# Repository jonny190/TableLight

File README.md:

# TableLight

A 3D-printable, battery-powered, USB-C rechargeable table lamp in the classic "Poldina" shape - honeycomb
disc base, thin stem, down-firing cone shade with a white top - running [WLED](https://kno.wled.ge/) on an
ESP32, with a capacitive touch pad hidden under the white top plate.

| | |
|---|---|
| Size | Ø118 x 36 mm base, Ø22 stem, shade Ø140 -> Ø104 x 120 mm, 279 mm tall overall |
| Light | 24-LED SK6812 RGBW (or WS2812B) ring under the head, shining down through a diffuser; optional second 16-LED ring |
| Power | 1 **or** 2 x 18650 Li-ion in parallel (1S) in the base, USB-C charging (1 A) in the base, runs while charging |
| Control | WLED app / web UI / Home Assistant + touch on the white top (ESP32 native touch) |
| Electronics | one custom Ø110 mm PCB in the base (KiCad board + PCBWay Gerber/BOM/CPL package included); flashes WLED over the same USB-C port |
| Runtime | ~5 h at full reading brightness, ~12 h at mood brightness with two 3500 mAh cells (half with one cell) |

## What is in this repository

```
cad/tablelight.py          parametric CAD (Python: trimesh + manifold) - ALL dimensions live here
cad/stl/                   ready-to-print STL files (6 parts)
hardware/pcb/              custom controller PCB: SKiDL circuit, KiCad 7 board (kicad/), PCBWay fab package
                           (fab/: Gerbers, drill, BOM, pick-and-place), board generator, design notes
firmware/wled/             WLED build override + settings for this lamp
docs/BOM.md                complete bill of materials (printed parts, electronics, hardware, consumables)
docs/PRINTING.md           print settings and orientation per part
docs/ASSEMBLY.md           step-by-step build
docs/WLED_SETUP.md         WLED configuration (pins, 2D matrix, touch button, battery, current limit)
docs/images/               renders, section drawing, PCB placement, block diagram
```

## The parts

| STL | Qty | What it does |
|---|---|---|
| `base_shell.stl` | 1 | Honeycomb-topped base disc: the PCB hangs under its deck (components facing down), USB-C, power switch and charge LEDs in the side wall, 1-2 x 18650 inside |
| `base_bottom_plate.stl` | 1 | Screw-on floor with rubber feet; remove it to reach the batteries, buttons and connectors |
| `stem.stl` | 1 | Ø22 hollow stem with a Ø40 foot flange; screwed to the deck from below, carries the wires to the head |
| `head_plate.stl` | 1 | White top: stem socket, two LED-ring channels on the underside, skirt that the shade screws to, touch-pad recess |
| `cone_shade.stl` | 1 | Opaque cone Ø140 -> Ø104, open at the bottom; 3 nubs hold the diffuser, 3 radial screws hold it to the head |
| `head_diffuser.stl` | 1 | Ø104 translucent disc 14 mm under the LED ring so you never see bare LEDs from below |

Section through the assembled lamp (all clearances are modelled, nothing is glued):

## Electronics in one picture

Power path: USB-C -> TP4056 charger -> 1S pack (DW01A/FS8205A protected) -> load-share (Schottky + P-FET)
-> `VSYS` -> MT3608 boost 5.1 V -> P-FET LED switch -> LED ring in the head (via the stem); `VSYS` -> 3.3 V LDO -> ESP32-WROOM-32E.
The USB-C data lines go to a CH340C with auto-reset, so WLED is flashed through the charging port.
A slide switch in the base wall is the hard off (about 80 uA drain). WLED's "relay pin" cuts the LED rail so
standby is only the ESP32.

See `hardware/pcb/README.md` for the design rationale and `hardware/pcb/SCHEMATIC.md` for every net.

## Build order (short version)

1. Print the six parts (`docs/PRINTING.md`). Fit 12 x M3 heat-set inserts.
2. Order the PCB: upload `hardware/pcb/fab/tablelight-gerbers.zip` to PCBWay (`hardware/pcb/fab/README.md` has the form values). Flash WLED (`docs/WLED_SETUP.md`).
3. Tape the LED ring into the head plate, stick the touch foil in its recess, run the wires down the stem (`docs/ASSEMBLY.md`).
4. Screw the stem to the deck, plug the PCB in, screw the PCB to the deck bosses, fit 1 or 2 cells, screw the floor on.
5. Push the diffuser up into the cone, screw the cone to the head, push the head onto the stem and fix it with two screws. Done.

## Regenerating the CAD / PCB files

```
pip install -r requirements.txt
python3 cad/tablelight.py                    # STLs -> cad/stl, renders -> docs/images
python3 hardware/pcb/tablelight_netlist.py   # tablelight.net, bom_pcb.csv, SCHEMATIC.md
python3 hardware/pcb/board_outline.py        # outline.dxf, placement.svg, PLACEMENT.md
python3 hardware/pcb/build_board.py          # KiCad board -> autoroute -> DRC -> fab/ (needs KiCad 7 + freerouting.jar)
python3 docs/block_diagram.py                # block_diagram.svg/.png
```

Change a value in the `P = dict(...)` block at the top of `cad/tablelight.py` (shade size and taper, stem length,
base diameter, honeycomb size, ring diameters...) and everything that depends on it - head socket, cone screw
positions, wall openings, PCB placement drawing - follows. The stem is 236 mm tall as printed; set `stem_len`
lower if your printer's Z is under 240 mm.

## Safety notes

* Cells in parallel must be the same model and within ~0.1 V of each other when inserted. Never mix a fresh
  and a flat cell.
* The board has over/under-voltage, over-current and short protection (DW01A + FS8205A), but a lamp is a closed
  plastic box: keep the WLED current limit at or below 1200 mA and do not leave it charging on a cushion.
* Use a 5 V USB-C supply rated 2 A or more when charging and running at the same time.

## License

MIT for the code and design files. WLED is licensed separately by its authors.

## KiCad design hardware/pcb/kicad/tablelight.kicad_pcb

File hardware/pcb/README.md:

# TableLight controller PCB

Round Ø110 mm, 2 layer, 1.6 mm FR4. Lives in the base, components facing down, screwed to four bosses
under the base deck. One board does everything: charging, protection, boost, ESP32 + WLED, USB flashing,
LED power switching, touch input, battery sensing.

**Ready to order:** `fab/tablelight-gerbers.zip` (+ `fab/tablelight-bom.csv`, `fab/tablelight-cpl.csv` for
assembly). Ordering parameters and a pre-order checklist are in `fab/README.md`. The KiCad 7 board is
`kicad/tablelight.kicad_pcb`: hand-placed, autorouted (freerouting, 2 layers, 58 vias), GND pours both
sides, KiCad DRC clean (0 unconnected, 0 clearance/edge/hole/courtyard errors; remaining report entries
are silkscreen cosmetics).

| File | What |
|---|---|
| `build_board.py` | **the board** (KiCad 7 pcbnew API): places every footprint from the table inside it, autoroutes with freerouting, pours GND, runs DRC, exports `fab/` |
| `kicad/tablelight.kicad_pcb` | the finished board; `kicad/drc_report.txt` is the DRC of exactly this file |
| `fab/` | PCBWay package: Gerbers + drill zip, assembly BOM, pick-and-place, ordering notes |
| `tablelight_netlist.py` | **the circuit** (SKiDL). Run it to regenerate the three files below |
| `tablelight.net` | KiCad netlist with footprints assigned. pcbnew: *File > Import Netlist* |
| `SCHEMATIC.md` | every net with every pin, plus per-component pin tables |
| `bom_pcb.csv` | PCB bill of materials (refs, values, example MPNs, footprints) |
| `board_outline.py` | reads the enclosure parameters and writes the three files below |
| `outline.dxf` | Edge.Cuts (Ø110 circle + centre wire slot) and reference layers. pcbnew: *File > Import > Graphics* |
| `placement.svg` / `PLACEMENT.md` | where the connectors, holders, module and keep-outs must go |

## Regenerating the board

```
sudo apt install kicad            # KiCad 7 (pcbnew Python module + kicad-cli)
curl -L -o hardware/pcb/tools/freerouting.jar \
     https://github.com/freerouting/freerouting/releases/download/v1.9.0/freerouting-1.9.0.jar
python3 hardware/pcb/build_board.py               # place -> route -> zones -> DRC -> fab/
```

`build_board.py` reads the circuit from `tablelight_netlist.py` and the mechanical constraints from
`cad/tablelight.py`; component positions are the `PLACEMENT` table at the top of the script (KiCad
coordinates, Y down, component side view). Change a position there and rerun: the router, pours, DRC and
Gerbers are regenerated. Design rules baked in: 0.25 mm signal / 0.8 mm power tracks, 0.2 mm clearance,
0.7/0.35 mm vias, 0.4 mm copper-to-edge, GND pour both layers with thermal reliefs.

Keep-outs that the script enforces: no copper under the module antenna (both layers), no copper on the
component side within 4 mm of the four mounting holes (screw heads), courtyards clear of the two
Keystone 1042 holders (87.6 x 21.7 mm each).

If you would rather lay it out by hand: import `tablelight.net` into an empty pcbnew, import `outline.dxf`
onto Edge.Cuts, and follow `PLACEMENT.md`. Power nets (`BAT+`, `CELL-`, `GND`, `VSYS`, `+5V`, `VLED`) carry
up to 2.5 A: 0.8 mm+ traces or pours. Height limits from the enclosure: 22 mm anywhere on the component
side, 9 mm inside the four boss zones, 3 mm of lead length on the solder side.

## Design notes and calculations

**Cells.** 1S, one or two 18650 in parallel. Parallel cells need no balancing; they must be the same model
and within ~0.1 V when inserted. `J5` is a JST-PH alternative for a wire-lead holder or a pouch cell.

**Protection.** DW01A + FS8205A, the same topology as the ubiquitous TP4056 module: the two FETs sit in the
cell-negative path, `CELL-` is the raw cell terminal and `GND` is the protected side. Over-discharge 2.4 V,
over-charge 4.3 V, over-current ~3 A (with the 8205A's 2 x 25 mOhm). Dissipation at 2.5 A: 0.3 W.

**Charger.** TP4056, `R3` = 1.2k -> 1.0 A. 2 x 3500 mAh charge in about 8 h, one cell in 4 h. Use `R3` = 2k
(0.58 A) if it will mostly be charged from a laptop port. Dissipation worst case (5 V - 3.0 V) x 1 A = 2 W at
the start of charge: give U2's pad a big pour, the IC throttles thermally anyway. `TEMP` is grounded (no NTC).
CC1/CC2 pull-downs (5.1k) so USB-C to USB-C cables and PD chargers supply 5 V.

**Load sharing.** `D1` (SS34) feeds `VSYS` from `VBUS` while plugged in; `Q2` (AO4407A, 12 mOhm) connects the
pack to `VSYS` only when `VBUS` is absent (gate tied to `VBUS`, `R8` pull-down). The charger therefore only
ever sees the cell, so termination works, and the lamp runs at full power while charging. Q2 drop at 2.5 A:
30 mV.

**Boost.** MT3608 at 1.2 MHz, `R9`/`R10` = 75k/10k -> 5.1 V. 4.7 uH / 4 A inductor, 2 x 22 uF in, 2 x 22 uF
out plus 100 uF on `VLED`. Practical continuous output from a 3.3 V cell is about 1.5 A at 5 V, hence the
WLED current limit of 1.2 A (24 + 16 LEDs at full white would ask for 2.4 A). `EN` is driven by `LED_EN`
(GPIO16), so the converter idles when the light is off.

**LED rail switch.** `Q3` (AO3401A) between `+5V` and `VLED`, driven by `Q4` (2N7002) from `LED_EN`. WLED's
"relay pin" feature raises GPIO16 whenever the strip is on. `R11` keeps the LEDs off during boot. With the
rail off the ring draws nothing, so standby is only the ESP32 (~80 mA with WiFi, ~10 mA with WiFi sleep).

**Level shifter.** SN74AHCT1G125 powered from `+5V`, input from GPIO2, 330 R into the data line. Its `OE#`
is tied to the Q3 gate node, so the data output is high-impedance while the rail is off - no back-powering
the ring through its data pin.

**3.3 V.** AP2112K-3.3 from `VSYS` (works from 3.0 to 5 V input, 250 mV dropout at 600 mA). Its `EN` pin is
the power switch `SW1`: OFF disables the LDO, the ESP32 dies, `LED_EN` falls, boost and LED rail switch off.
Off-state drain is about 80 uA (LDO + DW01 + the two 100k/100k dividers + the boost FB divider): years.

**USB-UART.** CH340C at 3.3 V (`V3` tied to `VCC`), no crystal. Standard NodeMCU auto-reset with two NPNs
(DTR/RTS -> EN/IO0) so esptool and the WLED web installer work hands-free. `SW2` RESET and `SW3` BOOT for
manual recovery. USBLC6-2SC6 on D+/D- is optional ESD protection.

**ESP32 pins.** GPIO2 LED data, GPIO16 LED rail enable (relay pin), GPIO4 (T0) touch, GPIO35 battery voltage
(100k/100k, x2.0), GPIO34 VBUS detect (100k/100k), GPIO25/26/32/33 on the expansion header `J4`. Strapping
pins 12 and 15 are left unconnected; GPIO0 has a 10k pull-up.

**Touch.** ESP32 native capacitive sensing through 2 mm of PLA with a Ø18 foil disc under the head plate.
`R22` (1k) is ESD/series protection; use 0 R if the sensitivity is marginal. The touch wire runs 250 mm down
the stem next to the LED wires: keep it away from the data wire if possible (twist it with the GND wire).

## Bring-up (bench, before installing)

1. No cells. Plug USB-C: D3 or D4 flashes, `VSYS` ~4.6 V, `3V3` = 3.3 V with `SW1` on, the CH340 enumerates.
2. Flash WLED. It should boot and start its AP.
3. Insert one cell. Unplug USB: the lamp keeps running from the cell (Q2). `BAT+` divider reads on GPIO35.
4. Connect the ring to `J2`, turn the light on in WLED: `VLED` = 5.1 V only while on.
5. Plug USB with the cell in: D3 (red) while charging, D4 (green) when done. Q2 should be cold.

## Ordering

See `fab/README.md` for the PCBWay form values. Any 2-layer service works (JLCPCB, Aisler, OSH Park take
the same zip). All SMD parts are on one side; the THT parts (JST headers, pin header, slide switch) and the
SMD-mount 18650 holders are a 20 minute hand solder if you do not order assembly.

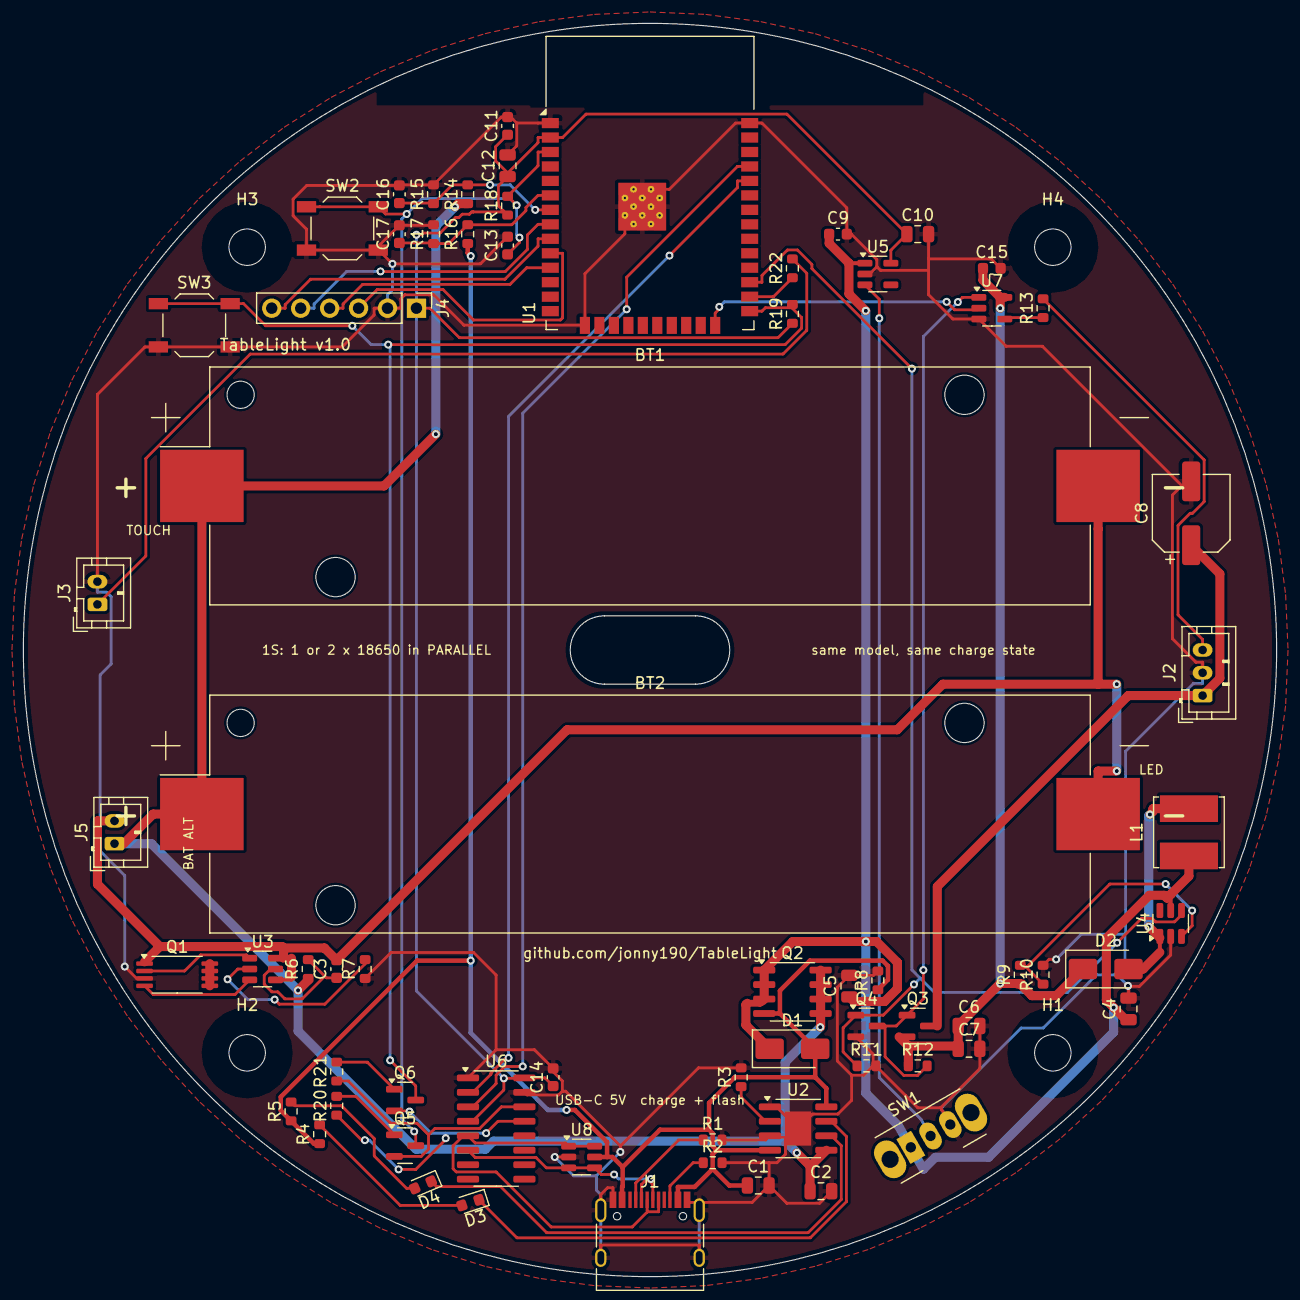
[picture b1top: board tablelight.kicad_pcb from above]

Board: 2 copper layers, 110.0 x 110.0 mm, 72 parts (0 on the bottom side), 46 nets.

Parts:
BT1: 18650; BatteryHolder_Keystone_1042_1x18650
BT2: 18650 (optional 2nd cell); BatteryHolder_Keystone_1042_1x18650
C1, C2, C10, C12: 10uF 10V; C_0805_2012Metric
C3, C11, C14, C15, C16, C17: 100nF; C_0603_1608Metric
C4, C5, C6, C7: 22uF 10V; C_0805_2012Metric
C8: 100uF 6.3V; CP_Elec_6.3x5.4
C9, C13: 1uF; C_0603_1608Metric
D1, D2: SS34; D_SMA
D3: RED; LED_0603_1608Metric
D4: GREEN; LED_0603_1608Metric
H1, H2, H3, H4: M3; MountingHole_3.2mm_M3
J1: USB-C 16P; USB_C_Receptacle_HRO_TYPE-C-31-M-12
J2: LED RING; JST_PH_B3B-PH-K_1x03_P2.00mm_Vertical
J3: TOUCH; JST_PH_B2B-PH-K_1x02_P2.00mm_Vertical
J4: EXP; PinHeader_1x06_P2.54mm_Vertical
J5: BAT ALT; JST_PH_B2B-PH-K_1x02_P2.00mm_Vertical
L1: 4.7uH 4A; L_Bourns_SRN6045TA
Q1: FS8205A; TSSOP-8_4.4x3mm_P0.65mm
Q2: AO4407A; SOIC-8_3.9x4.9mm_P1.27mm
Q3: AO3401A; SOT-23
Q4: 2N7002; SOT-23
Q5, Q6: MMBT3904; SOT-23
R1, R2: 5.1k; R_0603_1608Metric
R3: 1.2k; R_0603_1608Metric
R4, R5, R7, R22: 1k; R_0603_1608Metric
R6: 100R; R_0603_1608Metric
R8, R11, R14, R15, R16, R17: 100k; R_0603_1608Metric
R9: 75k; R_0603_1608Metric
R10, R12, R18, R19: 10k; R_0603_1608Metric
R13: 330R; R_0603_1608Metric
R20, R21: 12k; R_0603_1608Metric
SW1: POWER; SW_Slide_SPDT_Angled_CK_OS102011MA1Q
SW2: RESET; SW_SPST_TL3342
SW3: BOOT; SW_SPST_TL3342
U1: ESP32-WROOM-32E-N4; ESP32-WROOM-32
U2: TP4056; SOIC-8-1EP_3.9x4.9mm_P1.27mm_EP2.29x3mm
U3: DW01A; SOT-23-6
U4: MT3608; SOT-23-6
U5: AP2112K-3.3; SOT-23-5
U6: CH340C; SOIC-16_3.9x9.9mm_P1.27mm
U7: 74AHCT1G125; SOT-23-5
U8: USBLC6-2SC6; SOT-23-6

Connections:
3V3: C10.1, C11.1, C12.1, C14.1, J4.1, R18.1, R19.1, U1.2, U5.5, U6.4, U6.16
+5V: C6.1, C7.1, C15.1, D2.1, Q3.2, R9.1, R12.1, U7.5
BAT+: BT1.1, BT2.1, C2.1, J5.1, Q2.5, Q2.6, Q2.7, Q2.8, R6.1, R14.1, U2.5
BOOST_FB: R9.2, R10.1, U4.3
BOOST_SW: D2.2, L1.2, U4.1
CC1: J1.A5, R1.1
CC2: J1.B5, R2.1
CELL-: BT1.2, BT2.2, C3.2, J5.2, Q1.1, U3.4, U3.6
CHRG: D3.1, U2.7
DTR: Q6.2, R20.1, U6.13
DTR_B: Q5.1, R20.2
DW01_CS: R7.2, U3.2
DW01_OC: Q1.4, U3.3
DW01_OD: Q1.2, U3.1
DW01_VCC: C3.1, R6.2, U3.5
EN: C13.1, Q5.3, R18.2, SW2.1, U1.3
GND: C1.2, C2.2, C4.2, C5.2, C6.2, C7.2, C8.2, C9.2, C10.2, C11.2, C12.2, C13.2, C14.2, C15.2, C16.2, C17.2, J1.A1, J1.A12, J1.B1, J1.B12, J1.S1, J2.2, J3.2, J4.2, Q1.3, Q4.2, R1.2, R2.2, R3.2, R7.1, R8.2, R10.2, R11.2, R15.2, R17.2, SW1.3, SW2.2, SW3.2, U1.1, U1.15, U1.38, U1.39, U2.1, U2.3, U2.9, U4.2, U5.2, U6.1, U6.15, U7.3, U8.2
IO0: Q6.3, R19.2, SW3.1, U1.25
IO25: J4.3, U1.10
IO26: J4.4, U1.11
IO32: J4.5, U1.8
IO33: J4.6, U1.9
LED_DATA: U1.24, U7.2
LED_DATA_5V: R13.1, U7.4
LED_DOUT: J2.3, R13.2
LED_EN: Q4.1, R11.1, U1.27, U4.4
unnamed: R3.1, U2.2
unnamed: D3.2, R4.2
unnamed: D4.2, R5.2
PROT_FET_D: Q1.5, Q1.6, Q1.7, Q1.8
RTS: Q5.2, R21.1, U6.14
RTS_B: Q6.1, R21.2
STDBY: D4.1, U2.6
SYS_EN: SW1.2, U5.3
TOUCH: R22.1, U1.26
TOUCH_PAD: J3.1, R22.2
U0RXD: U1.34, U6.2
U0TXD: U1.35, U6.3
USB_D+: J1.A6, J1.B6, U6.5, U8.1, U8.6
USB_D-: J1.A7, J1.B7, U6.6, U8.3, U8.4
VBAT_SENSE: C16.1, R14.2, R15.1, U1.7
VBUS: C1.1, D1.2, J1.A4, J1.A9, J1.B4, J1.B9, Q2.4, R4.1, R5.1, R8.1, R16.1, U2.4, U2.8, U8.5
VBUS_DET: C17.1, R16.2, R17.1, U1.6
VLED: C8.1, J2.1, Q3.3
VSYS: C4.1, C5.1, C9.1, D1.1, L1.1, Q2.1, Q2.2, Q2.3, SW1.1, U4.5, U5.1
nLED_EN: Q3.1, Q4.3, R12.2, U7.1

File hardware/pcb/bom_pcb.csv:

Refs,Qty,Value,Description,MPN / example part,Footprint,Notes
BT1,1,18650,18650 PCB-mount holder,Keystone 1042 (or BH-18650-PC equiv.),BatteryHolder_Keystone_1042_1x18650,
BT2,1,18650 (optional 2nd cell),18650 PCB-mount holder,Keystone 1042 (or BH-18650-PC equiv.),BatteryHolder_Keystone_1042_1x18650,
"C1, C2, C10, C12",4,10uF 10V,Capacitor 0805 X5R,,C_0805_2012Metric,
"C3, C11, C14, C15, C16, C17",6,100nF,Capacitor 0603 X7R,,C_0603_1608Metric,
"C4, C5, C6, C7",4,22uF 10V,Capacitor 0805 X5R,,C_0805_2012Metric,
C8,1,100uF 6.3V,Electrolytic / polymer cap SMD 6.3x5.4,,CP_Elec_6.3x5.4,LED rail bulk
"C9, C13",2,1uF,Capacitor 0603 X7R,,C_0603_1608Metric,EN reset delay
"D1, D2",2,SS34,Schottky diode SMA,,D_SMA,USB -> VSYS
D3,1,RED,LED 0603,,LED_0603_1608Metric,CHRG: on while charging
D4,1,GREEN,LED 0603,,LED_0603_1608Metric,STDBY: on when charge complete
"H1, H2, H3, H4",4,M3,"M3 mounting hole (r=45 mm, 45/135/225/315 deg)",-,MountingHole_3.2mm_M3,
J1,1,USB-C 16P,"USB-C receptacle 16 pin, top mount",HRO TYPE-C-31-M-12,USB_C_Receptacle_HRO_TYPE-C-31-M-12,
J2,1,LED RING,JST PH 2.0 mm 3 pin,B3B-PH-K-S,JST_PH_B3B-PH-K_1x03_P2.00mm_Vertical,"1 = VLED (+5V), 2 = GND, 3 = DATA -> LED ring(s) in the head, via the stem"
J3,1,TOUCH,JST PH 2.0 mm 2 pin,B2B-PH-K-S,JST_PH_B2B-PH-K_1x02_P2.00mm_Vertical,"1 = pad, 2 = GND (optional shield)"
J4,1,EXP,Pin header 1x6 2.54 mm (expansion),generic,PinHeader_1x06_P2.54mm_Vertical,"3V3 GND IO25 IO26 IO32 IO33 (IR receiver, extra buttons, sensors)"
J5,1,BAT ALT,JST PH 2.0 mm 2 pin,B2B-PH-K-S,JST_PH_B2B-PH-K_1x02_P2.00mm_Vertical,"alternative: wire-lead holder / pouch cell, parallel to BT1/BT2"
L1,1,4.7uH 4A,Power inductor 6x6 mm shielded,,L_Bourns_SRN6045TA,"e.g. Bourns SRN6045TA-4R7Y or any 6x6 shielded, Isat >= 4 A"
Q1,1,FS8205A,"Dual N-MOSFET common drain, 20 V, 6 A (battery protection)",FS8205A,TSSOP-8_4.4x3mm_P0.65mm,
Q2,1,AO4407A,P-MOSFET -30 V 12 A 12 mOhm (load sharing),AO4407A,SOIC-8_3.9x4.9mm_P1.27mm,load-share P-FET; off while USB present
Q3,1,AO3401A,P-MOSFET -30 V 4 A (LED rail switch),AO3401A,SOT-23,LED rail switch
Q4,1,2N7002,N-MOSFET 60 V 300 mA,2N7002,SOT-23,inverts LED_EN for Q3
"Q5, Q6",2,MMBT3904,NPN transistor (auto-reset),MMBT3904,SOT-23,auto-reset: EN; auto-reset: IO0
"R1, R2",2,5.1k,Resistor 0603 1%,,R_0603_1608Metric,CC1 Rd -> sink advertises 5 V device; CC2 Rd
R3,1,1.2k,Resistor 0603 1%,,R_0603_1608Metric,PROG: 1.2k = 1.0 A charge; use 2k for 0.58 A (weak USB ports)
"R4, R5, R7, R22",4,1k,Resistor 0603 1%,,R_0603_1608Metric,DW01 CS sense; touch series / ESD; 0R also fine
R6,1,100R,Resistor 0603 1%,,R_0603_1608Metric,DW01 VCC filter
"R8, R11, R14, R15, R16, R17",6,100k,Resistor 0603 1%,,R_0603_1608Metric,LED_EN pull-down: LEDs off during boot; VBAT divider top (x2.0 in WLED battery usermod); VBUS bleed / Q2 gate pull-down; VBUS present detect
R9,1,75k,Resistor 0603 1%,,R_0603_1608Metric,FB divider: Vout = 0.6*(1+75/10) = 5.1 V
"R10, R12, R18, R19",4,10k,Resistor 0603 1%,,R_0603_1608Metric,Q3 gate pull-up
R13,1,330R,Resistor 0603 1%,,R_0603_1608Metric,LED data series termination
"R20, R21",2,12k,Resistor 0603 1%,,R_0603_1608Metric,
SW1,1,POWER,Slide switch SPDT right-angle THT (power),C&K OS102011MA1QN1,SW_Slide_SPDT_Angled_CK_OS102011MA1Q,ON = SYS_EN high; only switches the LDO enable (tiny current)
SW2,1,RESET,Tactile switch 3x6x2.5 mm SMD,TL3342 / TS-1187A,SW_SPST_TL3342,
SW3,1,BOOT,Tactile switch 3x6x2.5 mm SMD,TL3342 / TS-1187A,SW_SPST_TL3342,
U1,1,ESP32-WROOM-32E-N4,"ESP32-WROOM-32E-N4 WiFi/BT module, 4 MB flash",ESP32-WROOM-32E-N4,ESP32-WROOM-32,
U2,1,TP4056,"1 A linear Li-ion charger, ESOP-8",TP4056,SOIC-8-1EP_3.9x4.9mm_P1.27mm_EP2.29x3mm,
U3,1,DW01A,1S Li-ion protection IC,DW01A-G,SOT-23-6,
U4,1,MT3608,"Boost converter 2-24 V in, 1.2 MHz, 4 A switch",MT3608,SOT-23-6,
U5,1,AP2112K-3.3,LDO 3.3 V 600 mA low dropout,AP2112K-3.3TRG1,SOT-23-5,
U6,1,CH340C,"USB-UART bridge, internal oscillator",CH340C,SOIC-16_3.9x9.9mm_P1.27mm,
U7,1,74AHCT1G125,"Single bus buffer, 3.3->5 V level shift for LED data",SN74AHCT1G125DBVR,SOT-23-5,
U8,1,USBLC6-2SC6,USB ESD protection (optional),USBLC6-2SC6,SOT-23-6,optional ESD protection

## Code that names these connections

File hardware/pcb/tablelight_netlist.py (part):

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Load sharing: Schottky from VBUS to VSYS, P-FET (AO4407A) from pack to VSYS
   -> LEDs/ESP run from USB while charging; the charger sees only the cell.
VSYS -> MT3608 boost -> +5V (LED rail for the 24 (+16) LED rings, WLED current limit 1.2 A)
        -> AO3401A high-side switch -> VLED  (WLED "relay pin" GPIO16, true off)
VSYS -> AP2112K-3.3 LDO (EN = slide switch) -> 3V3 for the ESP32-WROOM-32E
USB data -> CH340C (3.3 V mode) -> UART0 with DTR/RTS auto-reset -> flash WLED over the same USB-C
74AHCT1G125 level shifter 3.3 -> 5 V for the LED data line (OE tied to the LED power switch)
ESP32 native capacitive touch on GPIO4 (T0) -> copper pad under the white head plate
Battery voltage divider -> GPIO35 for the WLED Battery usermod; VBUS detect -> GPIO34
"""
import csv
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DW_VCC, DW_CS = Net("DW01_VCC"), Net("DW01_CS")
OD, OC_ = Net("DW01_OD"), Net("DW01_OC")
SWN, FB = Net("BOOST_SW"), Net("BOOST_FB")
LED_EN = Net("LED_EN")       # GPIO16 (WLED relay pin, active high)
nLED_EN = Net("nLED_EN")     # gate of the LED P-FET / OE# of level shifter
LED_DATA = Net("LED_DATA")   # GPIO2, 3.3 V
LED_DATA5 = Net("LED_DATA_5V")
LED_OUT = Net("LED_DOUT")
TOUCH = Net("TOUCH")         # GPIO4 / T0
TOUCH_PAD = Net("TOUCH_PAD")
VBAT_S, VBUS_D = Net("VBAT_SENSE"), Net("VBUS_DET")
EN, IO0 = Net("EN"), Net("IO0")
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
